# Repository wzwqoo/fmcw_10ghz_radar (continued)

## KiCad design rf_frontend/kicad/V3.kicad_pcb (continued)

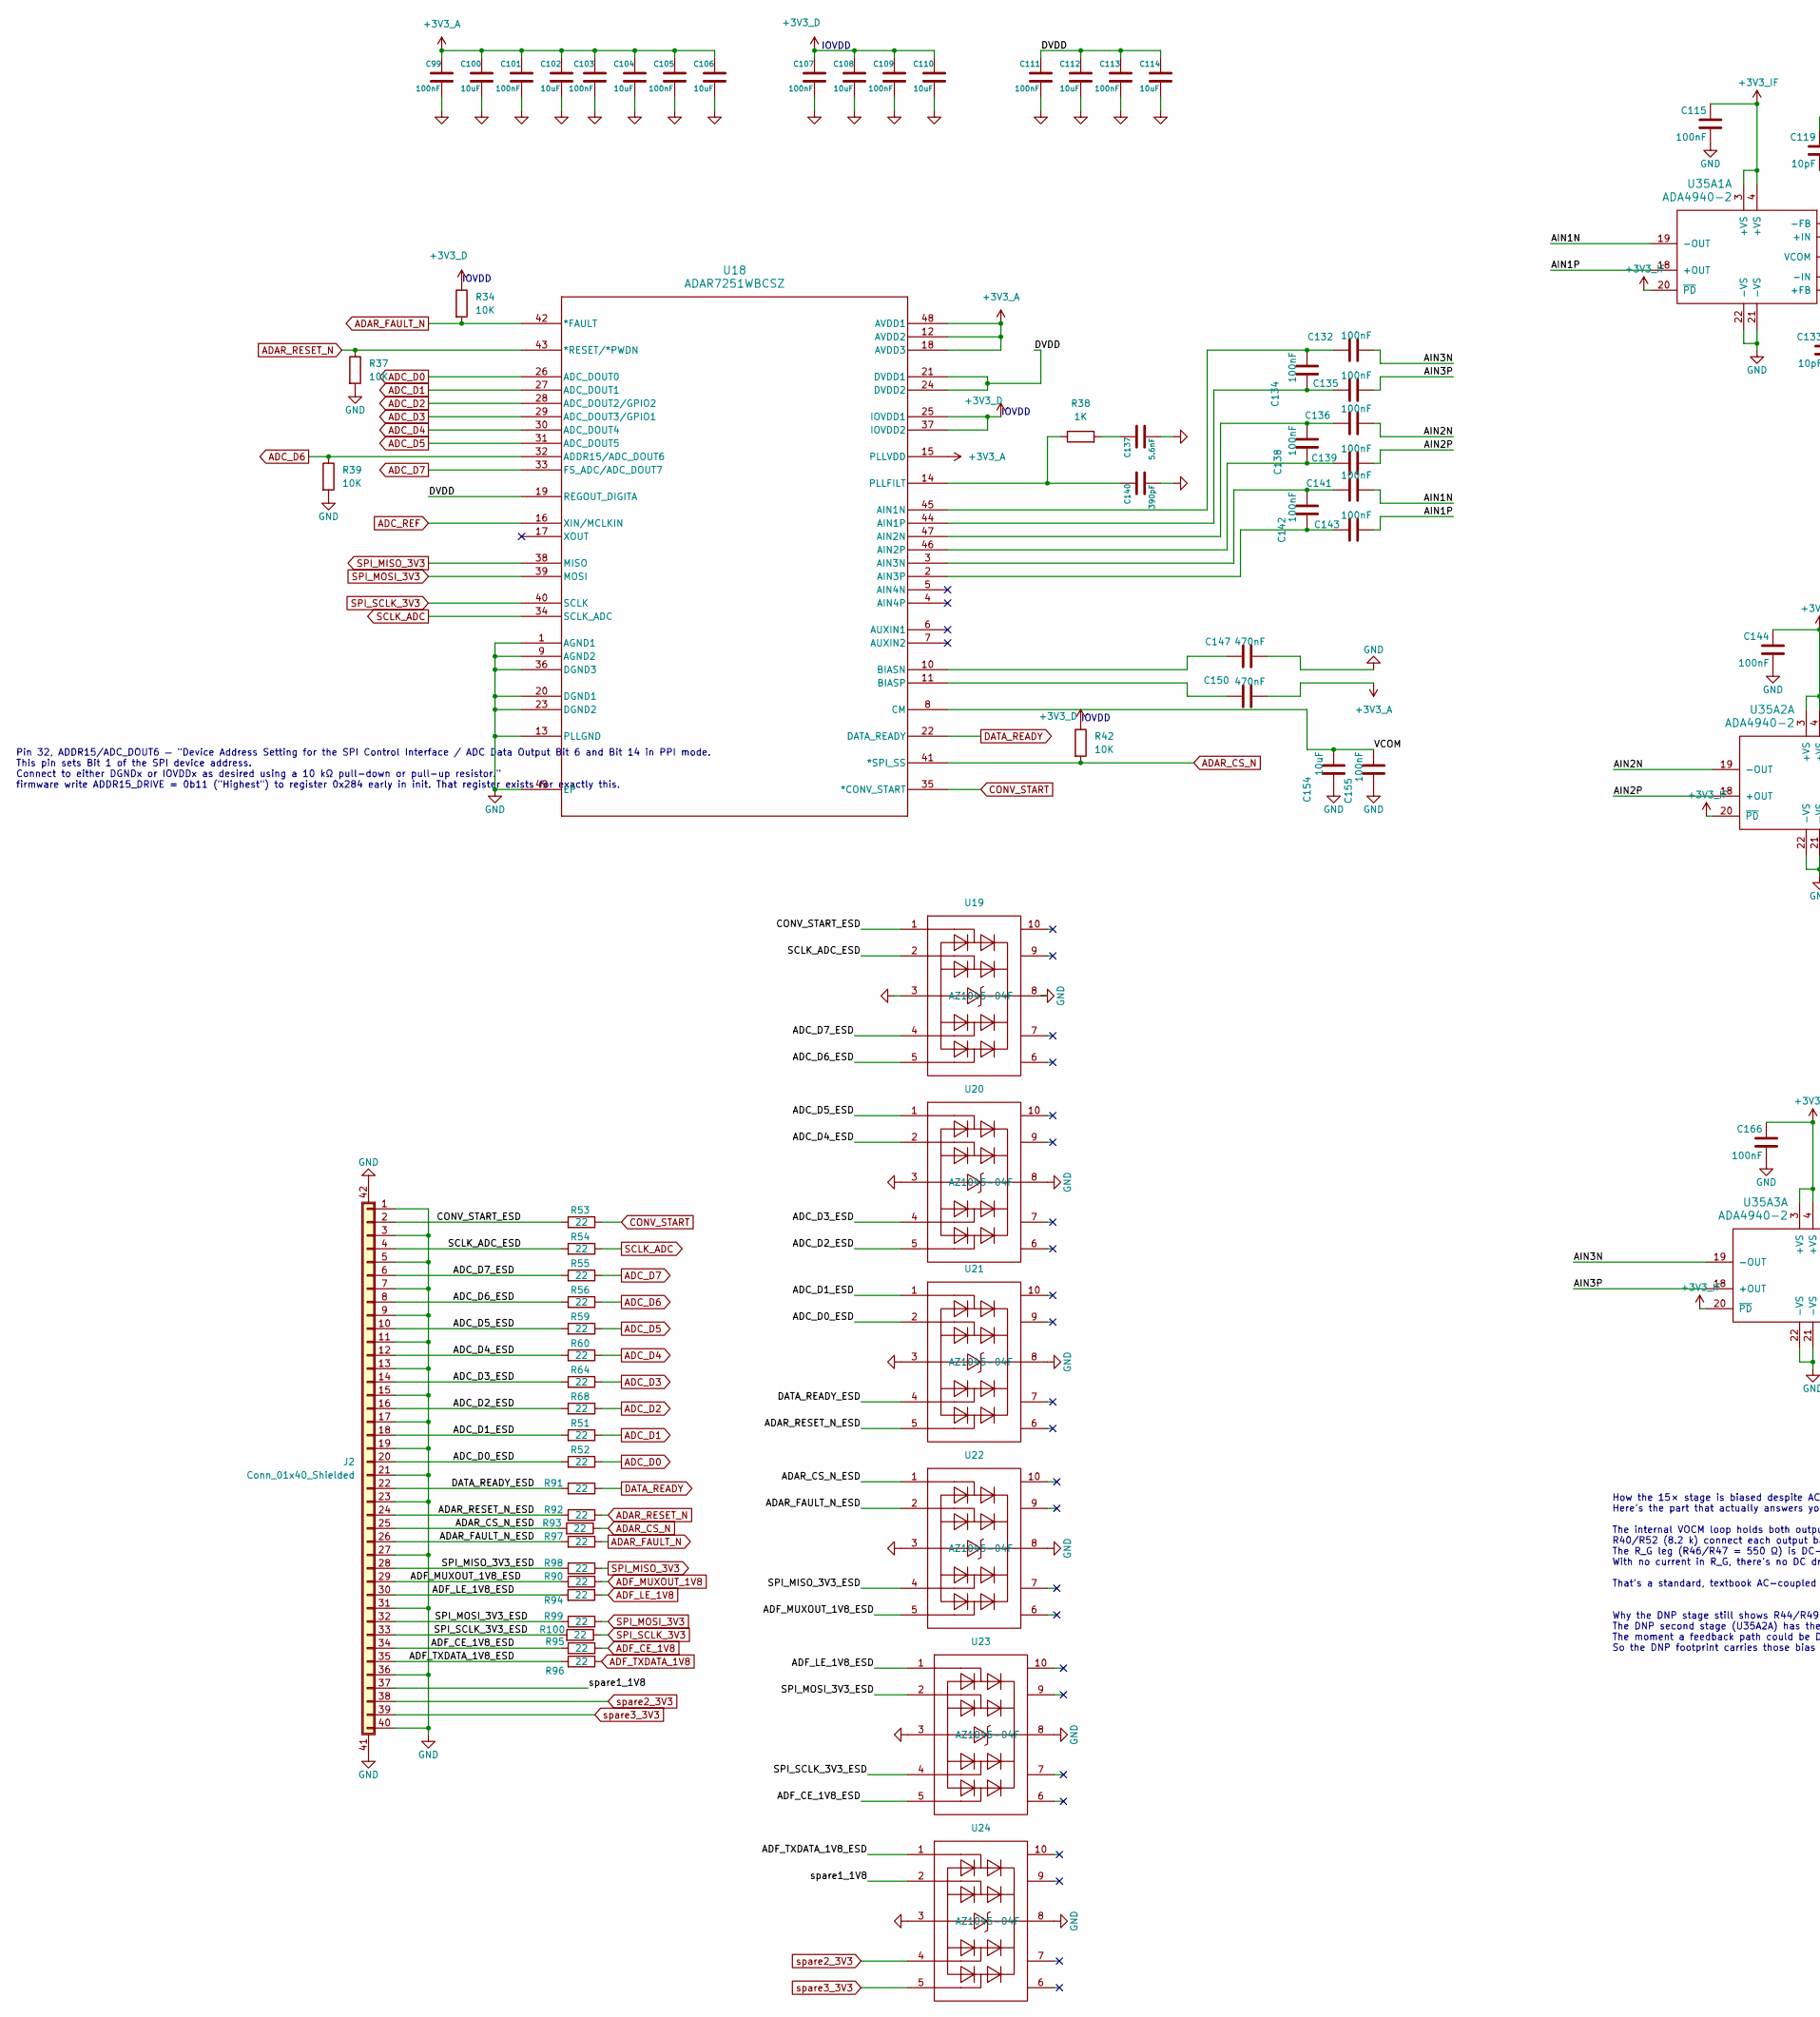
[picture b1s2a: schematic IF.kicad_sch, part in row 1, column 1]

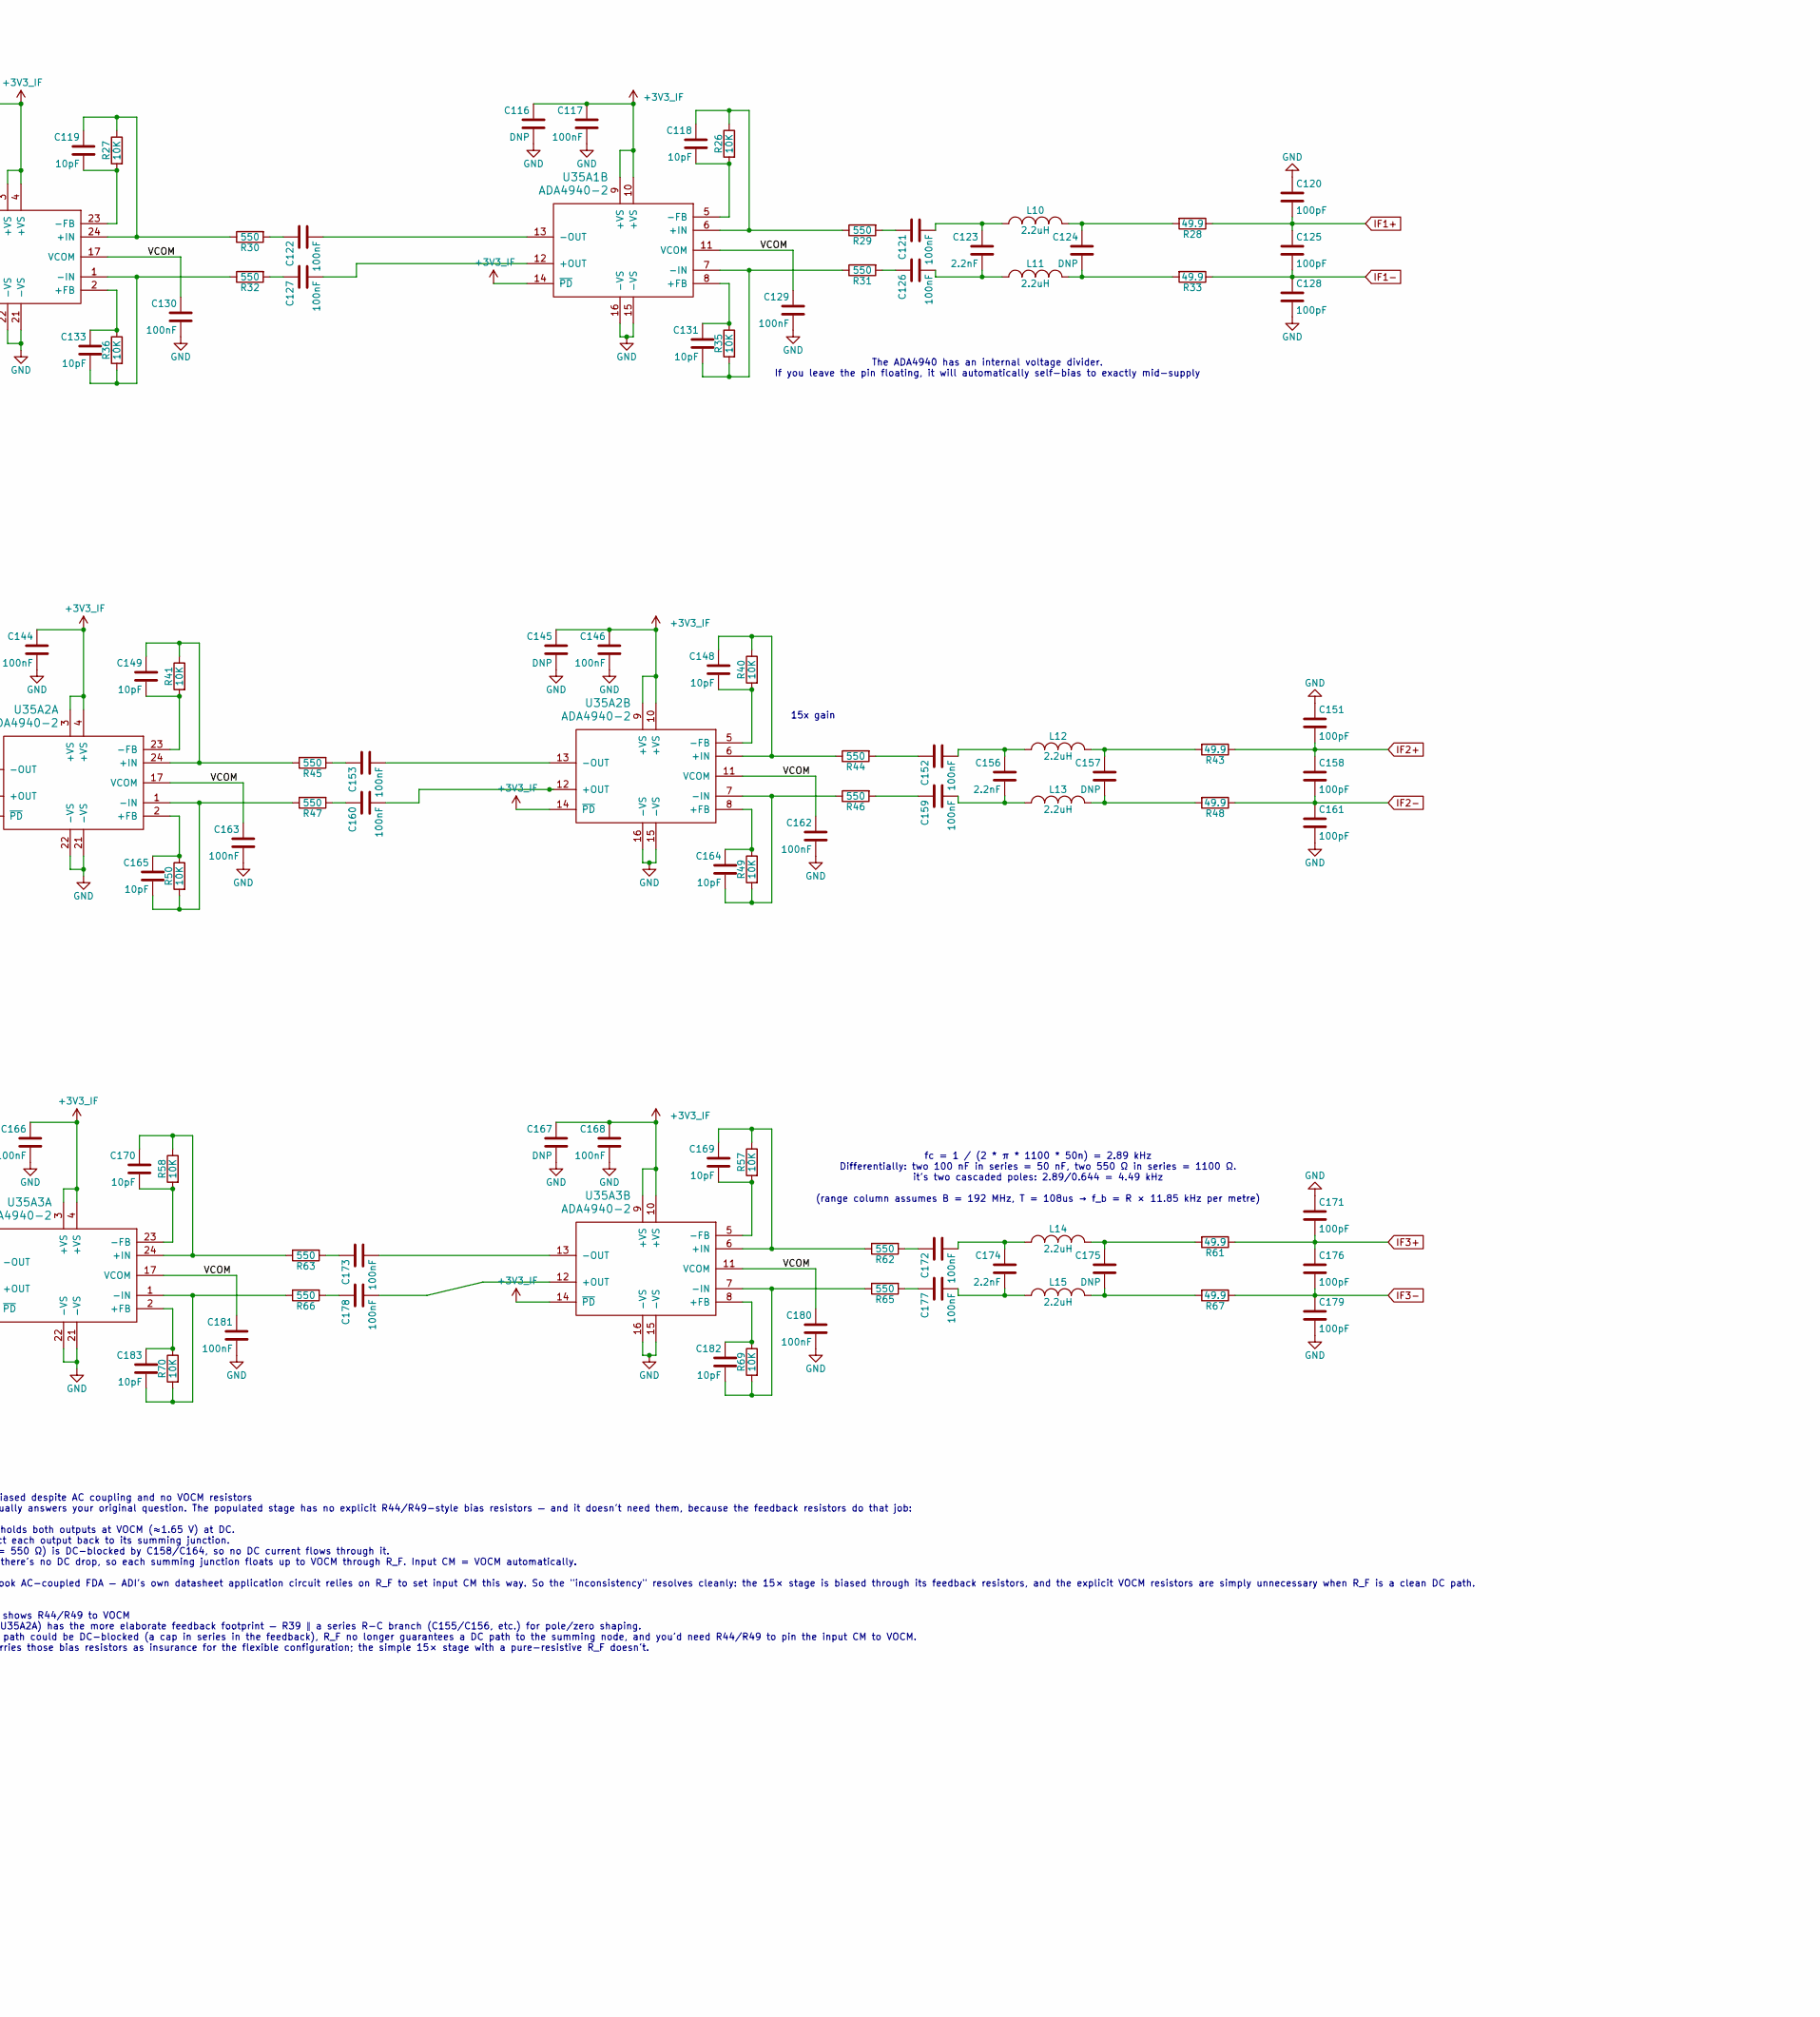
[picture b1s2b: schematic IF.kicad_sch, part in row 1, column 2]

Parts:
C99, C101, C103, C105, C107, C109, C111, C113, C115, C117, C121, C122, C126, C127, C129, C130, C132, C134, C135, C136, C138, C139, C141, C142, C143, C144, C146, C152, C153, C155, C159, C160, C162, C163, C166, C168, C172, C173, C177, C178, C180, C181: 100nF; C_0402_1005Metric
C100, C102, C104, C106, C108, C110, C112, C114, C154: 10uF; C_0805_2012Metric
C116, C124, C145, C157, C167, C175: DNP; C_0402_1005Metric
C118, C119, C131, C133, C148, C149, C164, C165, C169, C170, C182, C183: 10pF; C_0402_1005Metric
C120, C125, C128, C151, C158, C161, C171, C176, C179: 100pF; C_0402_1005Metric
C123, C156, C174: 2.2nF; C_0402_1005Metric
C137: 5.6nF; C_0402_1005Metric
C140: 390pF; C_0402_1005Metric
C147, C150: 470nF; C_0402_1005Metric
J2: Conn_01x40_Shielded; FPC-SMD_40P-P0.50_XUNPU_FPC-05FB-40PH20; Part# FPC-05FB-40PH20; LCSC Part # C2856837
L10, L11, L12, L13, L14, L15: 2.2uH; L_0805_2012Metric
R26, R27, R34, R35, R36, R37, R39, R40, R41, R42, R49, R50, R57, R58, R69, R70: 10K; R_0402_1005Metric
R28, R33, R43, R48, R61, R67: 49.9; R_0402_1005Metric
R29, R30, R31, R32, R44, R45, R46, R47, R62, R63, R65, R66: 550; R_0402_1005Metric
R38: 1K; R_0402_1005Metric
R51, R52, R53, R54, R55, R56, R59, R60, R64, R68, R90, R91, R92, R93, R94, R95, R96, R97, R98, R99, R100: 22; R_0402_1005Metric
U18: ADAR7251WBCSZ; ADAR7251_CS48_rounded_lands
U19, U20, U21, U22, U23, U24: AZ1045-04F
U35A1, U35A2, U35A3: ADA4940-2; LFCSP-24-1EP_4x4mm_P0.5mm_EP2.5x2.5mm

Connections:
+3V3_A: C99.1, C100.1, C101.1, C102.1, C103.1, C104.1, C105.1, C106.1, C150.2, U18.12 (AVDD2), U18.15 (PLLVDD), U18.18 (AVDD3), U18.48 (AVDD1); also elsewhere on the board
+3V3_D: C107.1, C108.1, C109.1, C110.1, R34.1, R42.1, U18.25 (IOVDD1), U18.37 (IOVDD2); also elsewhere on the board
+3V3_IF: C115.1, C116.1, C117.1, C144.1, C145.1, C146.1, C166.1, C167.1, C168.1, U35A1.3 (+VS), U35A1.4 (+VS), U35A1.9 (+VS), U35A1.10 (+VS), U35A1.14 (~PD), U35A1.20 (~PD), U35A2.3 (+VS), U35A2.4 (+VS), U35A2.9 (+VS), U35A2.10 (+VS), U35A2.14 (~PD), U35A2.20 (~PD), U35A3.3 (+VS), U35A3.4 (+VS), U35A3.9 (+VS), U35A3.10 (+VS), U35A3.14 (~PD), U35A3.20 (~PD); also elsewhere on the board
/IF/ADAR_CS_N_ESD: J2.25, R93.2, U22.1 (I/O_1)
/IF/ADAR_FAULT_N_ESD: J2.26, R97.2, U22.2 (I/O_2)
/IF/ADAR_RESET_N_ESD: J2.24, R92.2, U21.5 (I/O_4)
/IF/ADC_D0_ESD: J2.20, R52.2, U21.2 (I/O_2)
/IF/ADC_D1_ESD: J2.18, R51.2, U21.1 (I/O_1)
/IF/ADC_D2_ESD: J2.16, R68.2, U20.5 (I/O_4)
/IF/ADC_D3_ESD: J2.14, R64.2, U20.4 (I/O_3)
/IF/ADC_D4_ESD: J2.12, R60.2, U20.2 (I/O_2)
/IF/ADC_D5_ESD: J2.10, R59.2, U20.1 (I/O_1)
/IF/ADC_D6_ESD: J2.8, R56.2, U19.5 (I/O_4)
/IF/ADC_D7_ESD: J2.6, R55.2, U19.4 (I/O_3)
/IF/ADF_CE_1V8_ESD: J2.34, R95.2, U23.5 (I/O_4)
/IF/ADF_LE_1V8_ESD: J2.30, R94.2, U23.1 (I/O_1)
/IF/ADF_MUXOUT_1V8_ESD: J2.29, R90.2, U22.5 (I/O_4)
/IF/ADF_TXDATA_1V8_ESD: J2.35, R96.2, U24.1 (I/O_1)
/IF/AIN1N: C141.2, U35A1.19 (-OUT)
/IF/AIN1P: C143.2, U35A1.18 (+OUT)
/IF/AIN2N: C136.2, U35A2.19 (-OUT)
/IF/AIN2P: C139.2, U35A2.18 (+OUT)
/IF/AIN3N: C132.2, U35A3.19 (-OUT)
/IF/AIN3P: C135.2, U35A3.18 (+OUT)
/IF/CONV_START_ESD: J2.2, R53.2, U19.1 (I/O_1)
/IF/DATA_READY_ESD: J2.22, R91.2, U21.4 (I/O_3)
/IF/DVDD: C111.1, C112.1, C113.1, C114.1, U18.19 (REGOUT_DIGITA), U18.21 (DVDD1), U18.24 (DVDD2)
/IF/SCLK_ADC_ESD: J2.4, R54.2, U19.2 (I/O_2)
/IF/SPI_MISO_3V3_ESD: J2.28, R98.2, U22.4 (I/O_3)
/IF/SPI_MOSI_3V3_ESD: J2.32, R99.2, U23.2 (I/O_2)
/IF/SPI_SCLK_3V3_ESD: J2.33, R100.2, U23.4 (I/O_3)
/IF/VCOM: C129.1, C130.1, C154.2, C155.2, C162.1, C163.1, C180.1, C181.1, U18.8 (CM), U35A1.11 (VCOM), U35A1.17 (VCOM), U35A2.11 (VCOM), U35A2.17 (VCOM), U35A3.11 (VCOM), U35A3.17 (VCOM)
/IF/spare1_1V8: J2.37, U24.2 (I/O_2)
ADAR_CS_N: R42.2, R93.1, U18.41 (*SPI_SS)
ADAR_FAULT_N: R34.2, R97.1, U18.42 (*FAULT)
ADAR_RESET_N: R37.1, R92.1, U18.43 (*RESET/*PWDN)
ADC_D0: R52.1, U18.26 (ADC_DOUT0)
ADC_D1: R51.1, U18.27 (ADC_DOUT1)
ADC_D2: R68.1, U18.28 (ADC_DOUT2/GPIO2)
ADC_D3: R64.1, U18.29 (ADC_DOUT3/GPIO1)
ADC_D4: R60.1, U18.30 (ADC_DOUT4)
ADC_D5: R59.1, U18.31 (ADC_DOUT5)
ADC_D6: R39.1, R56.1, U18.32 (ADDR15/ADC_DOUT6)
ADC_D7: R55.1, U18.33 (FS_ADC/ADC_DOUT7)
ADC_REF: U18.16 (XIN/MCLKIN); also elsewhere on the board
ADF_CE_1V8: R95.1; also elsewhere on the board
ADF_LE_1V8: R94.1; also elsewhere on the board
ADF_MUXOUT_1V8: R90.1; also elsewhere on the board
ADF_TXDATA_1V8: R96.1; also elsewhere on the board
CONV_START: R53.1, U18.35 (*CONV_START)
DATA_READY: R91.1, U18.22 (DATA_READY)
GND: C99.2, C100.2, C101.2, C102.2, C103.2, C104.2, C105.2, C106.2, C107.2, C108.2, C109.2, C110.2, C111.2, C112.2, C113.2, C114.2, C115.2, C116.2, C117.2, C120.1, C128.2, C129.2, C130.2, C137.2, C140.2, C144.2, C145.2, C146.2, C147.2, C151.1, C154.1, C155.1, C161.2, C162.2, C163.2, C166.2, C167.2, C168.2, C171.1, C179.2, C180.2, C181.2, J2.1, J2.3, J2.5, J2.7, J2.9, J2.11, J2.13, J2.15, J2.17, J2.19, J2.21, J2.23, J2.27, J2.31, J2.36, J2.40, J2.41 (Shield), J2.42 (Shield), R37.2, R39.2, U18.1 (AGND1), U18.9 (AGND2), U18.13 (PLLGND), U18.20 (DGND1), U18.23 (DGND2), U18.36 (DGND3), U18.49 (EP), U19.3 (GND), U19.8 (GND), U20.3 (GND), U20.8 (GND), U21.3 (GND), U21.8 (GND), U22.3 (GND), U22.8 (GND), U23.3 (GND), U23.8 (GND), U24.3 (GND), U24.8 (GND), U35A1.15 (-VS), U35A1.16 (-VS), U35A1.21 (-VS), U35A1.22 (-VS), U35A1.25 (EP), U35A2.15 (-VS), U35A2.16 (-VS), U35A2.21 (-VS), U35A2.22 (-VS), U35A2.25 (EP), U35A3.15 (-VS), U35A3.16 (-VS), U35A3.21 (-VS), U35A3.22 (-VS), U35A3.25 (EP); also elsewhere on the board
IF1+: C120.2, C125.1, R28.1; also elsewhere on the board
IF1-: C125.2, C128.1, R33.1; also elsewhere on the board
IF2+: C151.2, C158.1, R43.1; also elsewhere on the board
IF2-: C158.2, C161.1, R48.1; also elsewhere on the board
IF3+: C171.2, C176.1, R61.1; also elsewhere on the board
IF3-: C176.2, C179.1, R67.1; also elsewhere on the board
unnamed: C121.1, R29.2
unnamed: C121.2, C123.1, L10.2
unnamed: C122.1, R30.2
unnamed: C123.2, C126.2, L11.2
unnamed: C124.1, L10.1, R28.2
unnamed: C124.2, L11.1, R33.2
unnamed: C126.1, R31.2
unnamed: C127.1, R32.2
unnamed: C137.1, R38.2
unnamed: C152.1, R44.2
unnamed: C152.2, C156.1, L12.2
unnamed: C153.1, R45.2
unnamed: C156.2, C159.2, L13.2
unnamed: C157.1, L12.1, R43.2
unnamed: C157.2, L13.1, R48.2
unnamed: C159.1, R46.2
unnamed: C160.1, R47.2
unnamed: C172.1, R62.2
unnamed: C172.2, C174.1, L14.2
unnamed: C173.1, R63.2
unnamed: C174.2, C177.2, L15.2
unnamed: C175.1, L14.1, R61.2
unnamed: C175.2, L15.1, R67.2
unnamed: C177.1, R65.2
unnamed: C178.1, R66.2
unnamed: C132.1, C134.2, U18.45 (AIN1N)
unnamed: C134.1, C135.1, U18.44 (AIN1P)
unnamed: C136.1, C138.2, U18.47 (AIN2N)
unnamed: C138.1, C139.1, U18.46 (AIN2P)
unnamed: C141.1, C142.2, U18.3 (AIN3N)
unnamed: C142.1, C143.1, U18.2 (AIN3P)
unnamed: C147.1, U18.10 (BIASN)
unnamed: C150.1, U18.11 (BIASP)
unnamed: C140.1, R38.1, U18.14 (PLLFILT)
unnamed: C133.1, R36.1, U35A1.2 (+FB)
unnamed: C119.1, R27.1, R30.1, U35A1.24 (+IN)
unnamed: C119.2, R27.2, U35A1.23 (-FB)
unnamed: C133.2, R32.1, R36.2, U35A1.1 (-IN)
unnamed: C131.1, R35.1, U35A1.8 (+FB)
unnamed: C118.1, R26.1, R29.1, U35A1.6 (+IN)
unnamed: C127.2, U35A1.12 (+OUT)
unnamed: C118.2, R26.2, U35A1.5 (-FB)
unnamed: C131.2, R31.1, R35.2, U35A1.7 (-IN)
unnamed: C122.2, U35A1.13 (-OUT)
unnamed: C165.1, R50.1, U35A2.2 (+FB)
unnamed: C149.1, R41.1, R45.1, U35A2.24 (+IN)
unnamed: C149.2, R41.2, U35A2.23 (-FB)
unnamed: C165.2, R47.1, R50.2, U35A2.1 (-IN)
unnamed: C164.1, R49.1, U35A2.8 (+FB)
unnamed: C148.1, R40.1, R44.1, U35A2.6 (+IN)
unnamed: C160.2, U35A2.12 (+OUT)
unnamed: C148.2, R40.2, U35A2.5 (-FB)
unnamed: C164.2, R46.1, R49.2, U35A2.7 (-IN)
unnamed: C153.2, U35A2.13 (-OUT)
unnamed: C183.1, R70.1, U35A3.2 (+FB)
unnamed: C170.1, R58.1, R63.1, U35A3.24 (+IN)
unnamed: C170.2, R58.2, U35A3.23 (-FB)
unnamed: C183.2, R66.1, R70.2, U35A3.1 (-IN)
unnamed: C182.1, R69.1, U35A3.8 (+FB)
unnamed: C169.1, R57.1, R62.1, U35A3.6 (+IN)
unnamed: C178.2, U35A3.12 (+OUT)
unnamed: C169.2, R57.2, U35A3.5 (-FB)
unnamed: C182.2, R65.1, R69.2, U35A3.7 (-IN)
unnamed: C173.2, U35A3.13 (-OUT)
SCLK_ADC: R54.1, U18.34 (SCLK_ADC)
SPI_MISO_3V3: R98.1, U18.38 (MISO)
SPI_MOSI_3V3: R99.1, U18.39 (MOSI); also elsewhere on the board
SPI_SCLK_3V3: R100.1, U18.40 (SCLK); also elsewhere on the board
spare2_3V3: J2.38, U24.4 (I/O_3)
spare3_3V3: J2.39, U24.5 (I/O_4)

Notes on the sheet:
IOVDD
The ADA4940 has an internal voltage divider. If you leave the pin floating, it will automatically self-bias to exactly mid-supply
fc = 1 / (2 * π * 1100 * 50n) = 2.89 kHz Differentially: two 100 nF in series = 50 nF, two 550 Ω in series = 1100 Ω. it's two cascaded poles: 2.89/0.644 = 4.49 kHz (range column assumes B = 192 MHz, T = 108us → f_b = R × 11.85 kHz per metre)
Pin 32, ADDR15/ADC_DOUT6 — "Device Address Setting for the SPI Control Interface / ADC Data Output Bit 6 and Bit 14 in PPI mode. This pin sets Bit 1 of the SPI device address. Connect to either DGNDx or IOVDDx as desired using a 10 kΩ pull-down or pull-up resistor." firmware write ADDR15_DRIVE = 0b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
15x gain
How the 15× stage is biased despite AC coupling and no VOCM resistors Here's the part that actually answers your original question. The populated stage has no explicit R44/R49-style bias resistors — and it doesn't need them, because the feedback resistors do that job: The internal VOCM loop holds b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

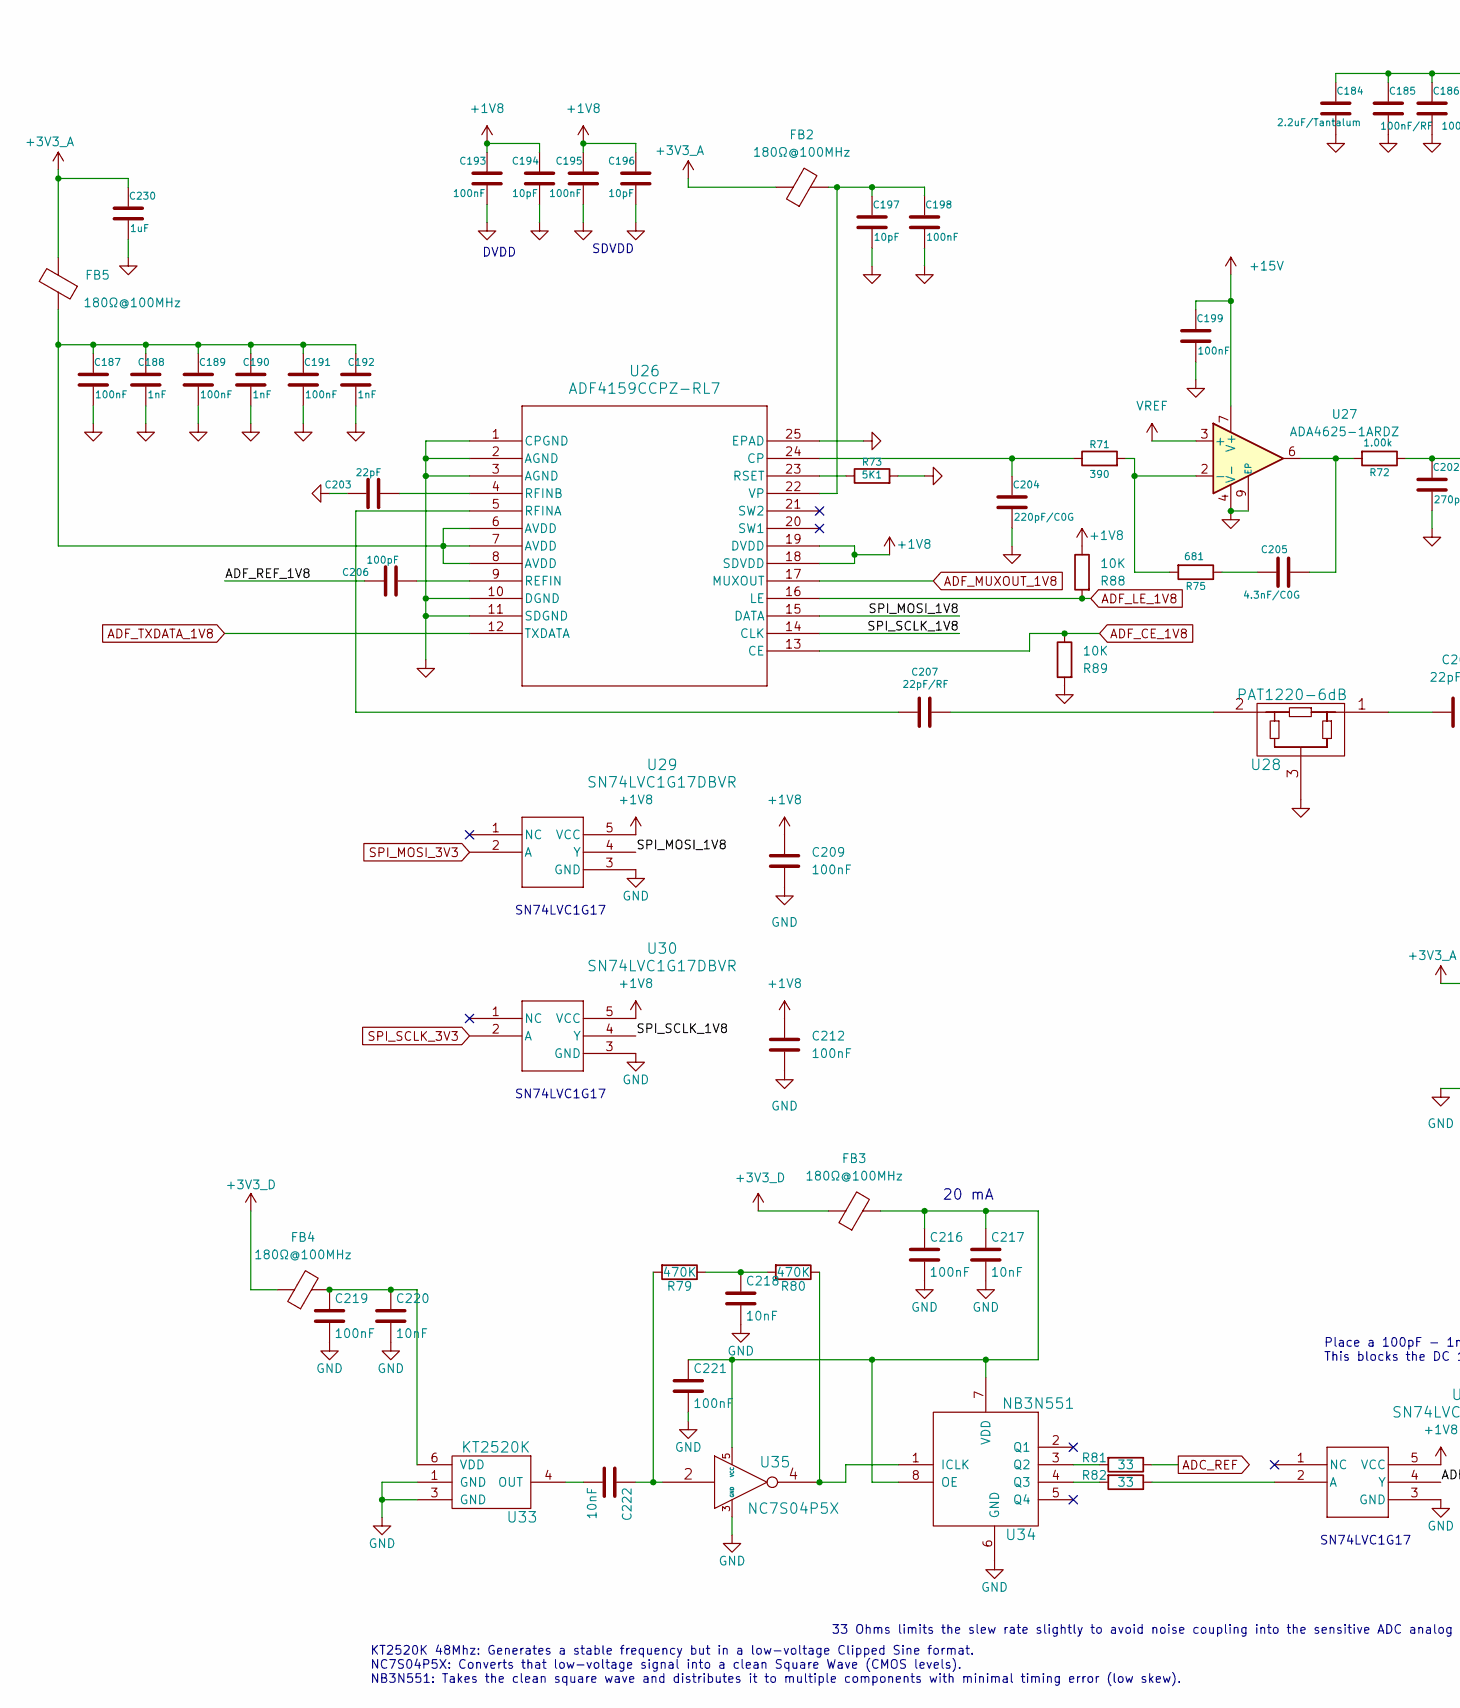
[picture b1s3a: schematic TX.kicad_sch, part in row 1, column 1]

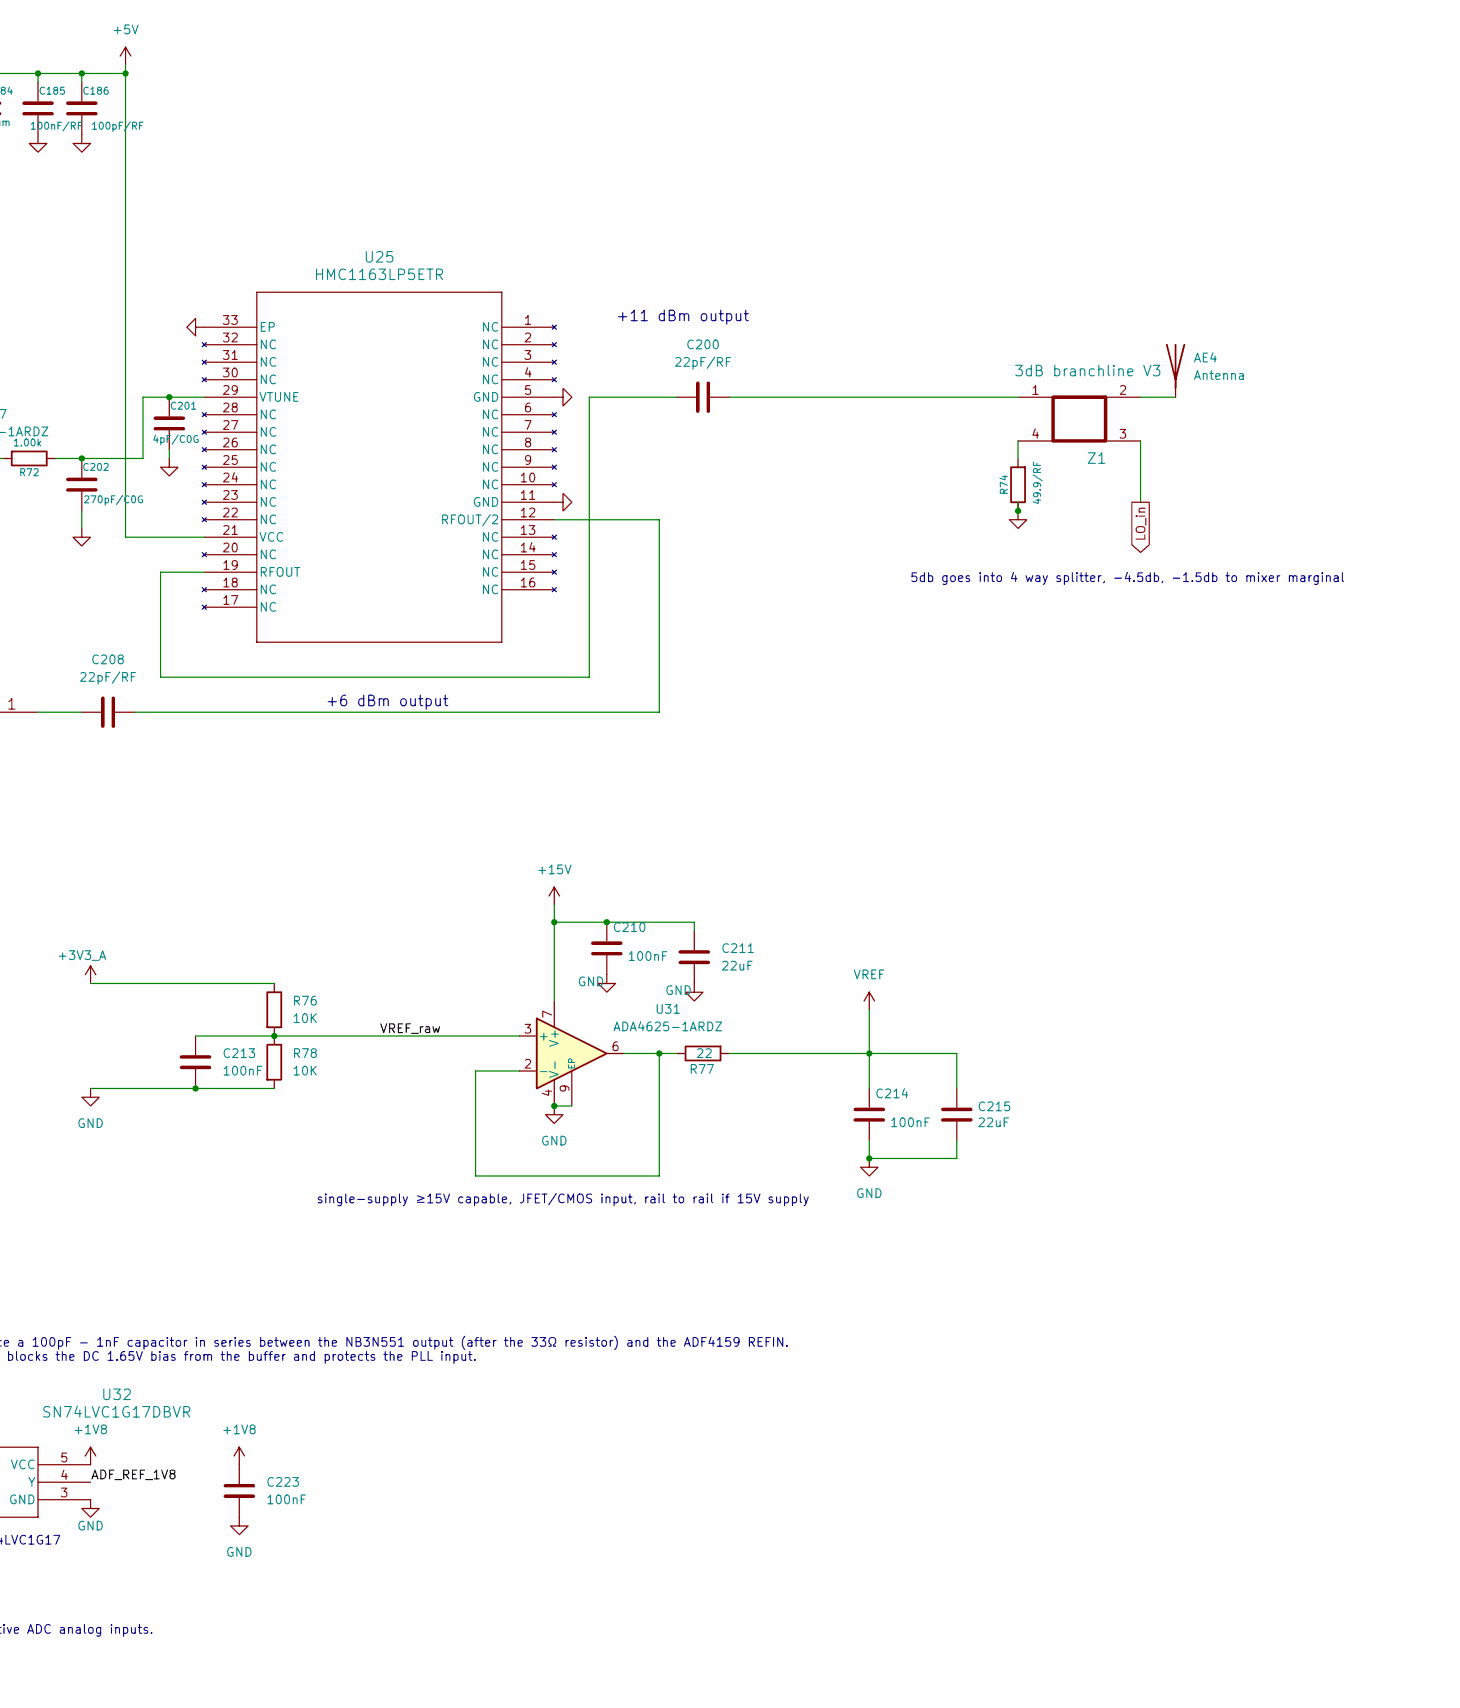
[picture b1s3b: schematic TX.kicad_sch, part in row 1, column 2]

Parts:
AE4: Antenna; antenna_v3
C184: 2.2uF/Tantalum; C_0805_2012Metric
C185: 100nF/RF; C_0402_1005Metric
C186: 100pF/RF; C_0402_1005Metric
C187, C189, C191, C193, C195, C198, C199, C209, C210, C212, C213, C214, C216, C219, C221, C223: 100nF; C_0402_1005Metric
C188, C190, C192: 1nF; C_0402_1005Metric
C194, C196, C197: 10pF; C_0402_1005Metric
C200, C207, C208: 22pF/RF; C_0201_0603Metric
C201: 4pF/C0G; C_0402_1005Metric
C202: 270pF/C0G; C_0402_1005Metric
C203: 22pF; C_0402_1005Metric
C204: 220pF/C0G; C_0402_1005Metric
C205: 4.3nF/C0G; C_0603_1608Metric
C206: 100pF; C_0402_1005Metric
C211, C215: 22uF; C_0805_2012Metric
C217, C218, C220, C222: 10nF; C_0402_1005Metric
C230: 1uF; C_0402_1005Metric
FB2, FB3, FB4, FB5: 180Ω@100MHz; L_0603_1608Metric; Part# BLM18PG181SN1D; LCSC Part # C82850
R71: 390; R_0402_1005Metric
R72: 1.00k; R_0402_1005Metric
R73: 5K1; R_0402_1005Metric
R74: 49.9/RF; R_0402_1005Metric
R75: 681; R_0402_1005Metric
R76, R78: 10K; R_0402_1005Metric; LCSC Part # x
R77: 22; R_0402_1005Metric; LCSC Part # C108406
R79, R80: 470K; R_0402_1005Metric
R81, R82: 33; R_0805_2012Metric
R88, R89: 10K; R_0402_1005Metric
U25: HMC1163LP5ETR; LFCSP-32-1EP_5x5mm_P0.5mm_EP3.1x3.1mm
U26: ADF4159CCPZ-RL7; LFCSP-24-1EP_4x4mm_P0.5mm_EP2.3x2.3mm
U27, U31: ADA4625-1ARDZ; SOIC-8-1EP_3.9x4.9mm_P1.27mm_EP2.29x3mm
U28: PAT1220-6dB; ATTN_PAT1220-C-1DB-T5
U29, U30, U32: SN74LVC1G17DBVR; SOT-23-5
U33: KT2520K; Oscillator_SMD_Kyocera_2520-6Pin_2.5x2.0mm
U34: NB3N551; DFN-8-1EP_6x5mm_P1.27mm_EP4x4mm
U35: NC7S04P5X; SOT-353_SC-70-5
Z1: 3dB branchline V3; branchline_v3

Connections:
+1V8: C193.1, C194.1, C195.1, C196.1, C209.1, C212.1, C223.1, R88.1, U26.18 (SDVDD), U26.19 (DVDD), U29.5 (VCC), U30.5 (VCC), U32.5 (VCC); also elsewhere on the board
+3V3_A: C230.1, FB2.1, FB5.2, R76.1; also elsewhere on the board
+3V3_D: FB3.1, FB4.1; also elsewhere on the board
+5V: C184.1, C185.1, C186.1, U25.21 (VCC); also elsewhere on the board
+15V: C199.1, C210.1, C211.1, U27.7 (V+), U31.7 (V+); also elsewhere on the board
/TX/ADF_REF_1V8: C206.1, U32.4 (Y)
/TX/SPI_MOSI_1V8: U26.15 (DATA), U29.4 (Y)
/TX/SPI_SCLK_1V8: U26.14 (CLK), U30.4 (Y)
/TX/VREF_raw: C213.1, R76.2, R78.1, U31.3 (+)
ADC_REF: R81.1; also elsewhere on the board
ADF_CE_1V8: R89.1, U26.13 (CE); also elsewhere on the board
ADF_LE_1V8: R88.2, U26.16 (LE); also elsewhere on the board
ADF_MUXOUT_1V8: U26.17 (MUXOUT); also elsewhere on the board
ADF_TXDATA_1V8: U26.12 (TXDATA); also elsewhere on the board
GND: C184.2, C185.2, C186.2, C187.2, C188.2, C189.2, C190.2, C191.2, C192.2, C193.2, C194.2, C195.2, C196.2, C197.2, C198.2, C199.2, C201.2, C202.2, C203.1, C204.2, C209.2, C210.2, C211.2, C212.2, C213.2, C214.2, C215.2, C216.2, C217.2, C218.2, C219.2, C220.2, C221.2, C223.2, C230.2, R73.2, R74.1, R78.2, R89.2, U25.5 (GND), U25.11 (GND), U25.33 (EP), U26.1 (CPGND), U26.2 (AGND), U26.3 (AGND), U26.10 (DGND), U26.11 (SDGND), U26.25 (EPAD), U27.4 (V-), U27.9 (EP), U28.3, U29.3 (GND), U30.3 (GND), U31.4 (V-), U31.9 (EP), U32.3 (GND), U33.1 (GND), U33.3 (GND), U34.6 (GND), U34.9 (EP), U35.3 (GND); also elsewhere on the board
LO_in: Z1.3; also elsewhere on the board
unnamed: AE4.1, Z1.2
unnamed: C187.1, C188.1, C189.1, C190.1, C191.1, C192.1, FB5.1, U26.6 (AVDD), U26.7 (AVDD), U26.8 (AVDD)
unnamed: C200.2, Z1.1
unnamed: C205.1, R75.1
unnamed: C205.2, R72.2, U27.6
unnamed: C207.1, U28.2
unnamed: C208.1, U28.1
unnamed: C218.1, R79.1, R80.2
unnamed: C222.1, R79.2, U35.2
unnamed: R74.2, Z1.4
unnamed: C200.1, U25.19 (RFOUT)
unnamed: C208.2, U25.12 (RFOUT/2)
unnamed: C201.1, C202.1, R72.1, U25.29 (VTUNE)
unnamed: C204.1, R71.1, U26.24 (CP)
unnamed: C206.2, U26.9 (REFIN)
unnamed: C207.2, U26.5 (RFINA)
unnamed: C203.2, U26.4 (RFINB)
unnamed: R73.1, U26.23 (RSET)
unnamed: C197.1, C198.1, FB2.2, U26.22 (VP)
unnamed: R71.2, R75.2, U27.2 (-)
unnamed: R77.1, U31.2 (-), U31.6
unnamed: R82.1, U32.2 (A)
unnamed: C222.2, U33.4 (OUT)
unnamed: C219.1, C220.1, FB4.2, U33.6 (VDD)
unnamed: R80.1, U34.1 (ICLK), U35.4
unnamed: C216.1, C217.1, C221.1, FB3.2, U34.7 (VDD), U34.8 (OE), U35.5 (VCC)
unnamed: R81.2, U34.3 (Q2)
unnamed: R82.2, U34.4 (Q3)
SPI_MOSI_3V3: U29.2 (A); also elsewhere on the board
SPI_SCLK_3V3: U30.2 (A); also elsewhere on the board
VREF: C214.1, C215.1, R77.2, U27.3 (+)

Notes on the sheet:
33 Ohms limits the slew rate slightly to avoid noise coupling into the sensitive ADC analog inputs.
Place a 100pF - 1nF capacitor in series between the NB3N551 output (after the 33Ω resistor) and the ADF4159 REFIN. This blocks the DC 1.65V bias from the buffer and protects the PLL input.
SN74LVC1G17
single-supply ≥15V capable, JFET/CMOS input, rail to rail if 15V supply
DVDD
KT2520K 48Mhz: Generates a stable frequency but in a low-voltage Clipped Sine format. NC7S04P5X: Converts that low-voltage signal into a clean Square Wave (CMOS levels). NB3N551: Takes the clean square wave and distributes it to multiple components with minimal timing error (low skew).
+11 dBm output
+6 dBm output
SDVDD
5db goes into 4 way splitter, -4.5db, -1.5db to mixer marginal
20 mA
